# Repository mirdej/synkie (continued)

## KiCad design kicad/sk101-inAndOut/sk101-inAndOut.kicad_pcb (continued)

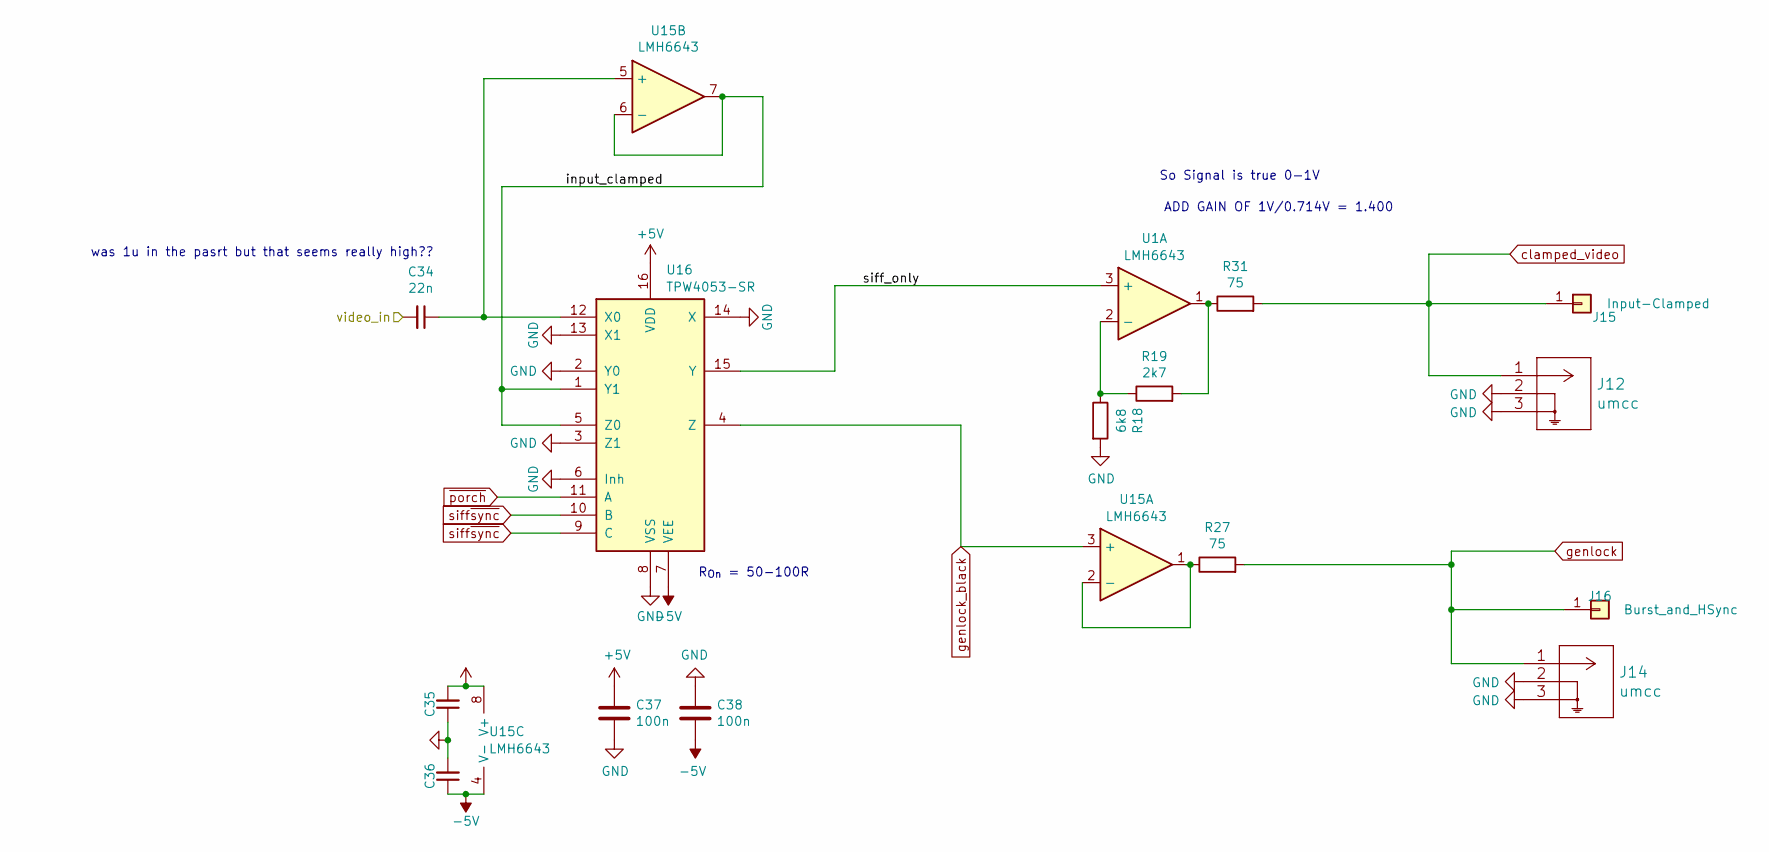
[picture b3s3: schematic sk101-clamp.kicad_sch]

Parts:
C34: 22n; C_0805_2012Metric_Pad1.15x1.40mm_HandSolder; LCSC C1729
C35, C36, C37, C38: 100n; C_0603_1608Metric; LCSC C14663
J12, J14: umcc; TE_UMCC_2337019-1; LCSC C5137195
J15: Input-Clamped; TestPoint_THTPad_D4.0mm_Drill2.0mm
J16: Burst_and_HSync; TestPoint_THTPad_D4.0mm_Drill2.0mm
R18: 6k8; R_0603_1608Metric; LCSC C23212
R19: 2k7; R_0603_1608Metric; LCSC C13167
R27, R31: 75; R_0603_1608Metric; LCSC C4275
U1, U15: LMH6643; VSSOP-8_3x3mm_P0.65mm; LCSC C478382
U16: TPW4053-SR; SOIC-16_3.9x9.9mm_P1.27mm; LCSC C7500846

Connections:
+5V: C35.2, C37.1, U15.8 (V+), U16.16 (VDD); also elsewhere on the board
-5V: C36.1, C38.2, U15.4 (V-), U16.7 (VEE); also elsewhere on the board
/Backporch-Clamp/input_clamped: U15.6 (-), U15.7, U16.1 (Y1), U16.5 (Z0)
/Backporch-Clamp/siff_only: U1.3 (+), U16.15 (Y)
/video_input_bufferd: C34.2; also elsewhere on the board
GND: C35.1, C36.2, C37.2, C38.1, J12.2, J12.3, J14.2, J14.3, R18.2, U16.2 (Y0), U16.3 (Z1), U16.6 (Inh), U16.8 (VSS), U16.13 (X1), U16.14 (X); also elsewhere on the board
unnamed: R19.2, R31.1, U1.1
unnamed: R18.1, R19.1, U1.2 (-)
unnamed: R27.1, U15.1, U15.2 (-)
unnamed: C34.1, U15.5 (+), U16.12 (X0)
clamped_video: J12.1, J15.1 (Pin_1_1), R31.2; also elsewhere on the board
genlock: J14.1, J16.1 (Pin_1_1), R27.2; also elsewhere on the board
genlock_black: U15.3 (+), U16.4 (Z); also elsewhere on the board
siff~sync: U16.9 (C), U16.10 (B); also elsewhere on the board
~porch: U16.11 (A); also elsewhere on the board

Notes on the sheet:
ADD GAIN OF 1V/0.714V = 1.400
So Signal is true 0-1V
R_{On} = 50-100R
was 1u in the pasrt but that seems really high??

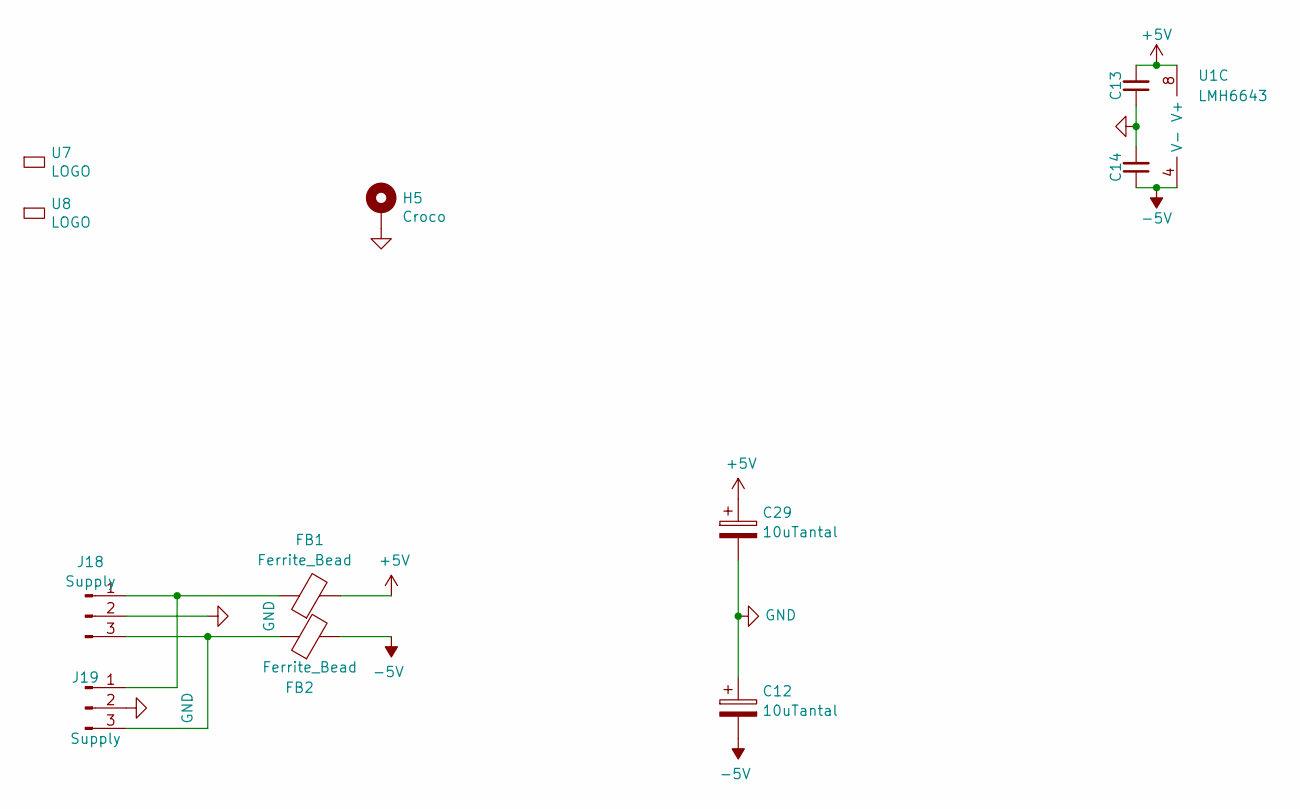
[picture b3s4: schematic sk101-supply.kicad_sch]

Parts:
C12, C29: 10uTantal; CP_EIA-3216-18_Kemet-A; LCSC C7171
C13, C14: 100n; C_0603_1608Metric; LCSC C14663
FB1, FB2: Ferrite_Bead; L_0805_2012Metric_Pad1.15x1.40mm_HandSolder; LCSC C1017
H5: Croco; CrocodileGroundPad
J18: Supply; Hirose_DF13-03P-1.25DSA_1x03_P1.25mm_Vertical
J19: Supply; Molex_KK-254_AE-6410-03A_1x03_P2.54mm_Vertical
U1: LMH6643; VSSOP-8_3x3mm_P0.65mm; LCSC C478382
U7: LOGO; logo_anyma
U8: LOGO; OSHW-Logo2_7.3x6mm_SilkScreen

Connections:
+5V: C13.2, C29.1, FB1.2, U1.8 (V+); also elsewhere on the board
-5V: C12.2, C14.1, FB2.2, U1.4 (V-); also elsewhere on the board
GND: C12.1, C13.1, C14.2, C29.2, H5.1 (1_1), J18.2, J19.2; also elsewhere on the board
unnamed: FB1.1, J18.1, J19.1
unnamed: FB2.1, J18.3, J19.3

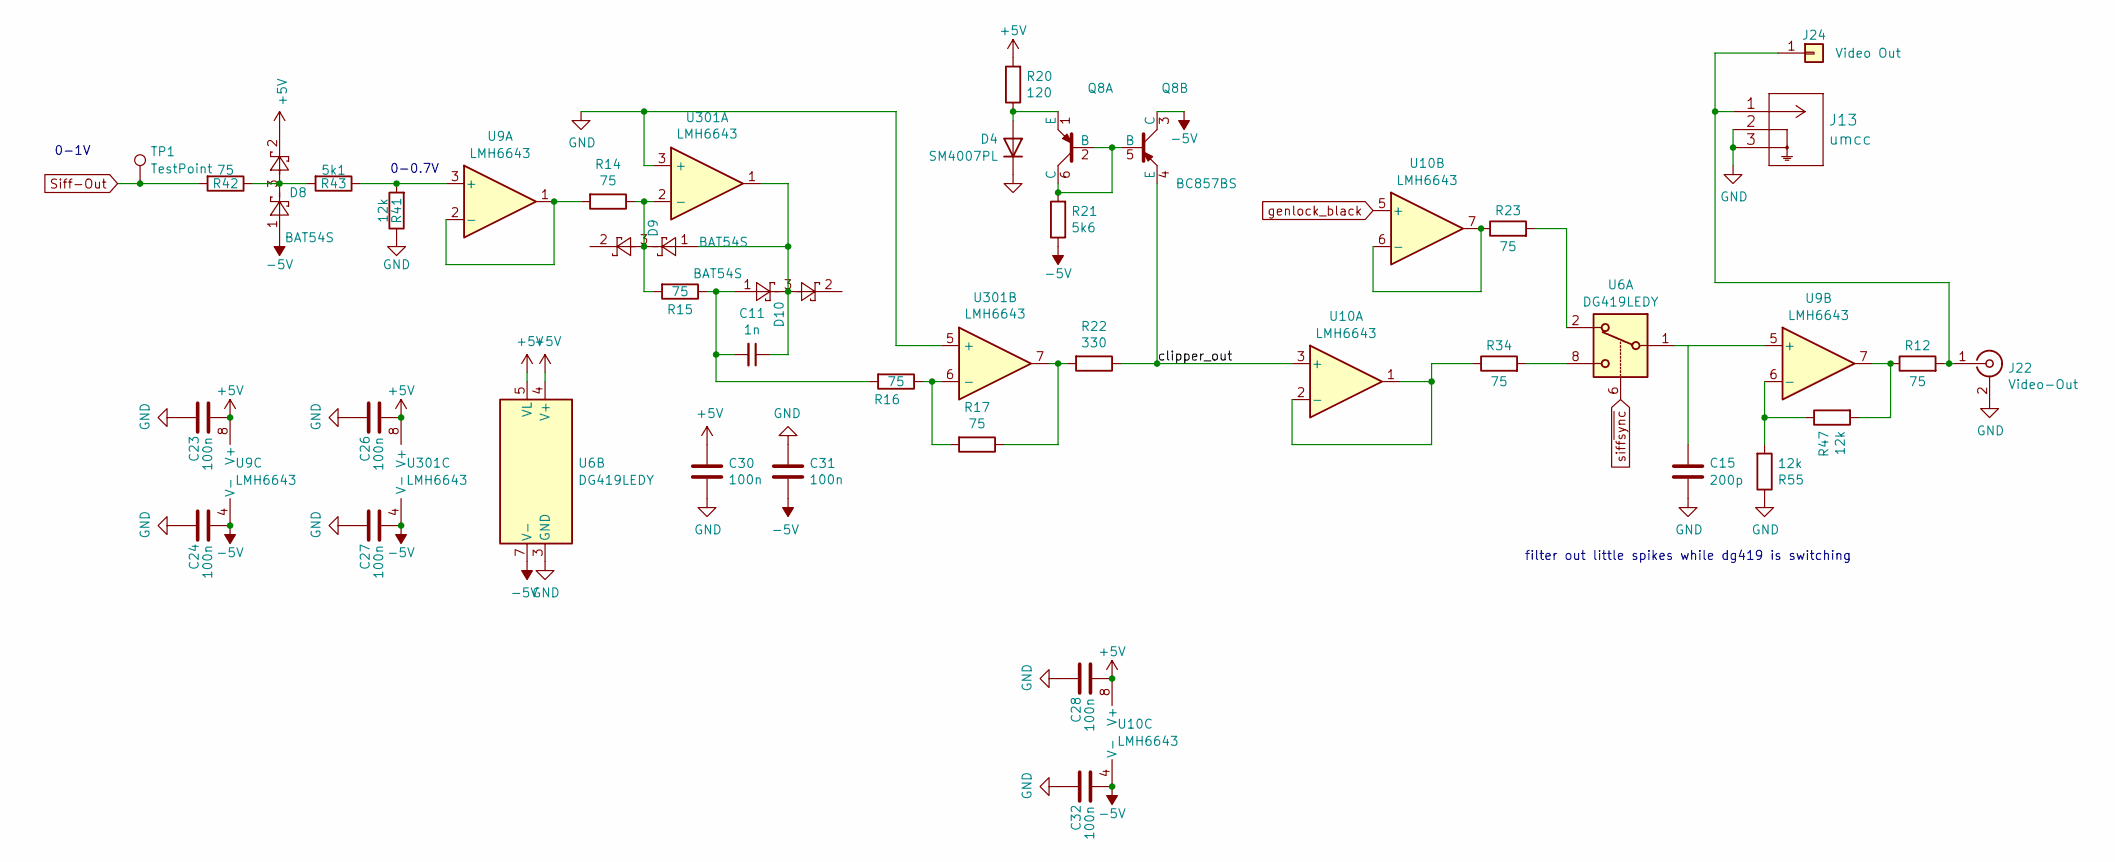
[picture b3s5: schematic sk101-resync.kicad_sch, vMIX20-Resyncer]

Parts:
C11: 1n; C_0603_1608Metric; LCSC C1588
C15: 200p; C_0603_1608Metric_Pad1.05x0.95mm_HandSolder; LCSC C1603
C23, C24, C26, C27, C28, C30, C31, C32: 100n; C_0603_1608Metric; LCSC C14663
D4: SM4007PL; D_SOD-123F; LCSC C64898
D8, D9, D10: BAT54S; SOT-23; LCSC C7420333
J13: umcc; TE_UMCC_2337019-1; LCSC C5137195
J22: Video-Out; BNC_Aliexpress
J24: Video Out; TestPoint_THTPad_D4.0mm_Drill2.0mm
Q8: BC857BS; SOT-363_SC-70-6_Handsoldering; LCSC C22381405
R12, R14, R15, R16, R17, R23, R34, R42: 75; R_0603_1608Metric; LCSC C4275
R20: 120; R_0603_1608Metric; LCSC C22787
R21: 5k6; R_0603_1608Metric; LCSC C23189
R22: 330; R_0603_1608Metric; LCSC C23138
R41, R47, R55: 12k; R_0603_1608Metric; LCSC C22790
R43: 5k1; R_0603_1608Metric; LCSC C23186
TP1: TestPoint; TestPoint_THTPad_D4.0mm_Drill2.0mm
U6: DG419LEDY; SOIC-8_3.9x4.9mm_P1.27mm; LCSC C2673265
U9, U10, U301: LMH6643; VSSOP-8_3x3mm_P0.65mm; LCSC C478382

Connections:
+5V: C23.2, C26.2, C28.2, C30.1, D8.2, R20.2, U6.4 (V+), U6.5 (VL), U9.8 (V+), U10.8 (V+), U301.8 (V+); also elsewhere on the board
-5V: C24.2, C27.2, C31.2, C32.2, D8.1, Q8.3 (C), R21.1, U6.7 (V-), U9.4 (V-), U10.4 (V-), U301.4 (V-); also elsewhere on the board
/Resyncer/clipper_out: Q8.4 (E), R22.1, U10.3 (+)
GND: C15.2, C23.1, C24.1, C26.1, C27.1, C28.1, C30.2, C31.1, C32.1, D4.1 (K), J13.2, J13.3, J22.2 (Ext), R41.1, R55.1, U6.3 (GND), U301.3 (+), U301.5 (+); also elsewhere on the board
unnamed: C11.1, D9.1, D10.3, U301.1
unnamed: C11.2, D10.1, R15.1, R16.2
unnamed: D4.2 (A), Q8.1 (E), R20.1
unnamed: D8.3, R42.1, R43.2
unnamed: J13.1, J22.1 (In), J24.1 (Pin_1_1), R12.2
unnamed: Q8.2 (B), Q8.5 (B), Q8.6 (C), R21.2
unnamed: R12.1, R47.2, U9.7
unnamed: R17.1, R22.2, U301.7
unnamed: R23.2, U6.2
unnamed: R34.2, U6.8
unnamed: R41.2, R43.1, U9.3 (+)
unnamed: R14.2, U9.1, U9.2 (-)
unnamed: C15.1, U6.1, U9.5 (+)
unnamed: R47.1, R55.2, U9.6 (-)
unnamed: R34.1, U10.1, U10.2 (-)
unnamed: R23.1, U10.6 (-), U10.7
unnamed: D9.3, R14.1, R15.2, U301.2 (-)
unnamed: R16.1, R17.2, U301.6 (-)
Siff-Out: R42.2, TP1.1 (1_1); also elsewhere on the board
genlock_black: U10.5 (+); also elsewhere on the board
siff~sync: U6.6; also elsewhere on the board

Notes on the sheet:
0-1V
filter out little spikes while dg419 is switching
0-0.7V

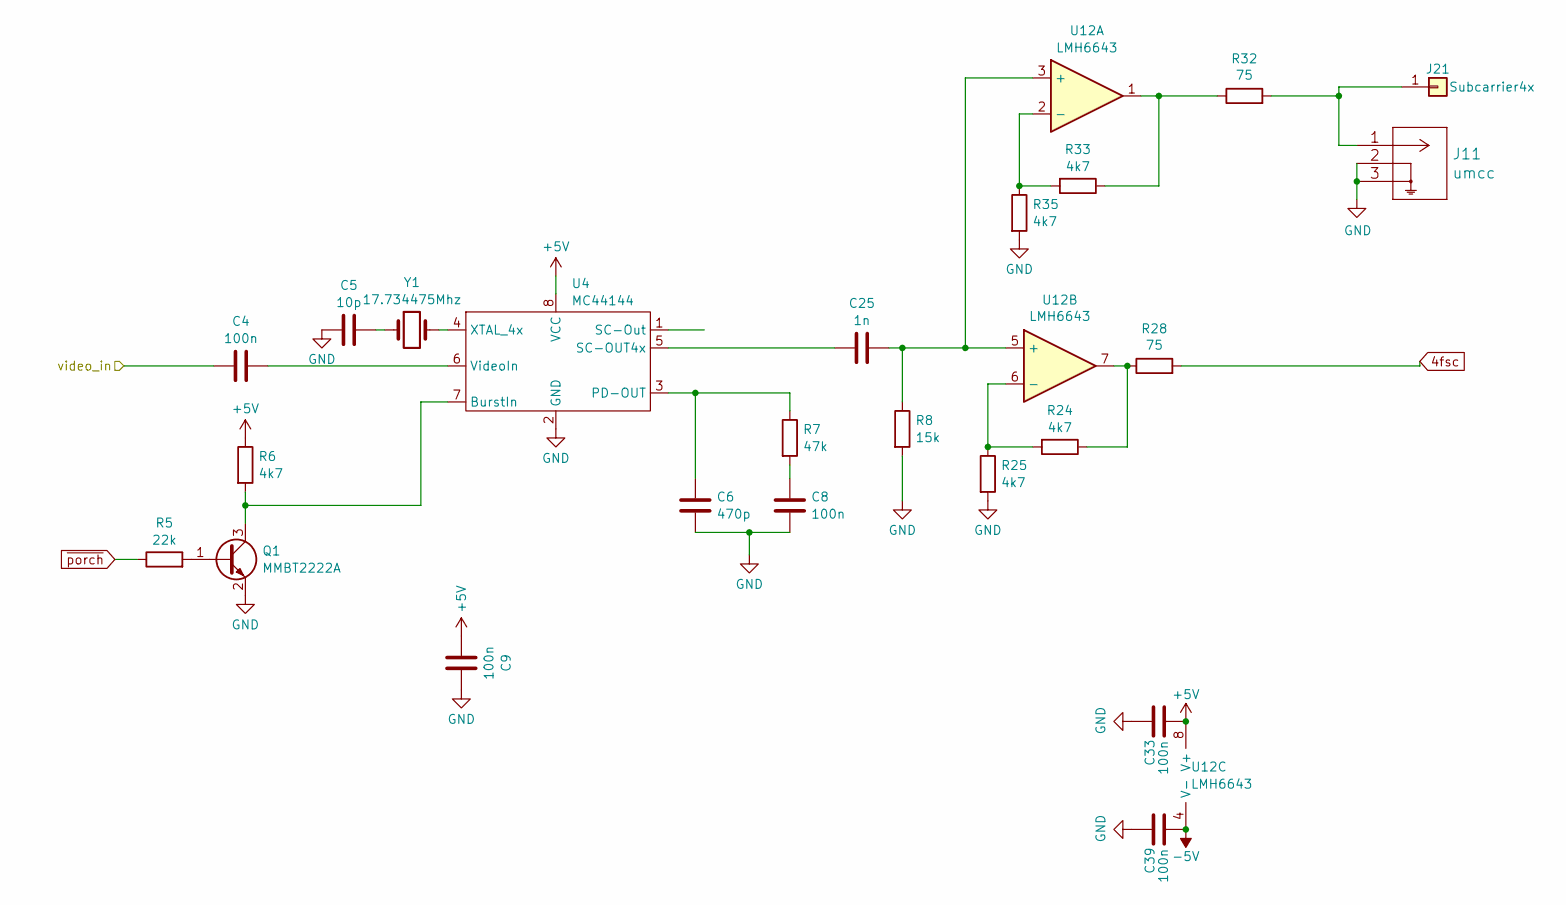
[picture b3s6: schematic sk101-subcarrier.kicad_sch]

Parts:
C4, C8, C9, C33, C39: 100n; C_0603_1608Metric; LCSC C14663
C5: 10p; C_0603_1608Metric; LCSC C1634
C6: 470p; C_0603_1608Metric; LCSC C1620
C25: 1n; C_0603_1608Metric; LCSC C1588
J11: umcc; TE_UMCC_2337019-1; LCSC C5137195
J21: Subcarrier4x; TestPoint_THTPad_D4.0mm_Drill2.0mm
Q1: MMBT2222A; SOT-23; LCSC C8512
R5: 22k; R_0603_1608Metric; LCSC C31850
R6, R24, R25, R33, R35: 4k7; R_0603_1608Metric; LCSC C23162
R7: 47k; R_0603_1608Metric; LCSC C25819
R8: 15k; R_0603_1608Metric; LCSC C22809
R28, R32: 75; R_0603_1608Metric; LCSC C4275
U4: MC44144; SOIC-8_3.9x4.9mm_P1.27mm
U12: LMH6643; VSSOP-8_3x3mm_P0.65mm; LCSC C478382
Y1: 17.734475Mhz; Crystal_SMD_HC49-SD; LCSC C22464815

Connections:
4fsc: R28.2; also elsewhere on the board
+5V: C9.1, C33.2, R6.1, U4.8 (VCC), U12.8 (V+); also elsewhere on the board
-5V: C39.2, U12.4 (V-); also elsewhere on the board
/video_input_bufferd: C4.1; also elsewhere on the board
GND: C5.1, C6.2, C8.2, C9.2, C33.1, C39.1, J11.2, J11.3, Q1.2 (E), R8.2, R25.2, R35.2, U4.2 (GND); also elsewhere on the board
unnamed: C5.2, Y1.1
unnamed: C8.1, R7.2
unnamed: J11.1, J21.1 (Pin_1_1), R32.2
unnamed: Q1.1 (B), R5.2
unnamed: Q1.3 (C), R6.2, U4.7 (BurstIn)
unnamed: R24.1, R28.1, U12.7
unnamed: R32.1, R33.1, U12.1
unnamed: C6.1, R7.1, U4.3 (PD-OUT)
unnamed: C25.1, U4.5 (SC-OUT4x)
unnamed: C4.2, U4.6 (VideoIn)
unnamed: U4.4 (XTAL_4x), Y1.2
unnamed: C25.2, R8.1, U12.3 (+), U12.5 (+)
unnamed: R33.2, R35.1, U12.2 (-)
unnamed: R24.2, R25.1, U12.6 (-)
~porch: R5.1; also elsewhere on the board

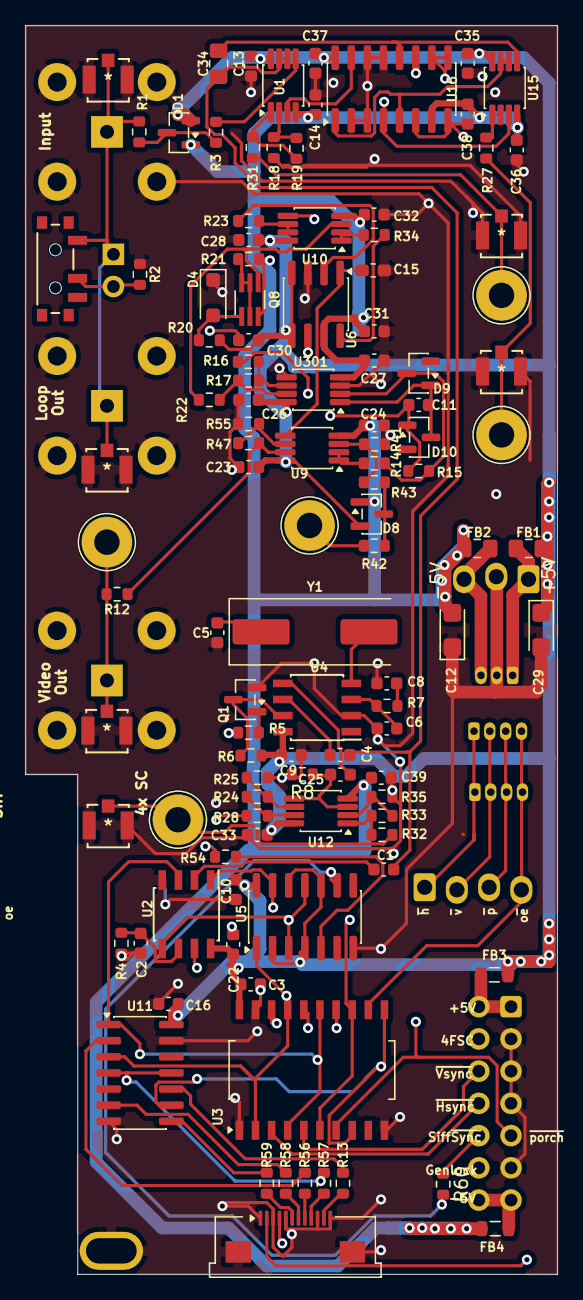
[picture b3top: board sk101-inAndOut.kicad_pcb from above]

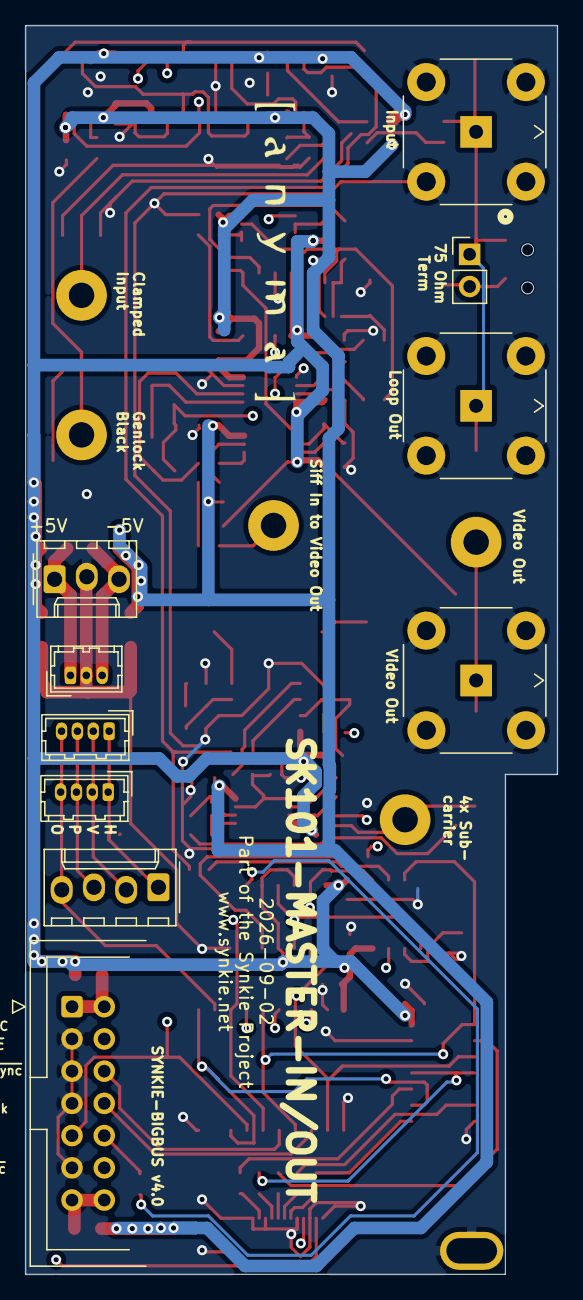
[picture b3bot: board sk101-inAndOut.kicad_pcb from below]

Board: 4 copper layers, 41.9 x 98.4 mm, 124 parts (12 on the bottom side), 83 nets.

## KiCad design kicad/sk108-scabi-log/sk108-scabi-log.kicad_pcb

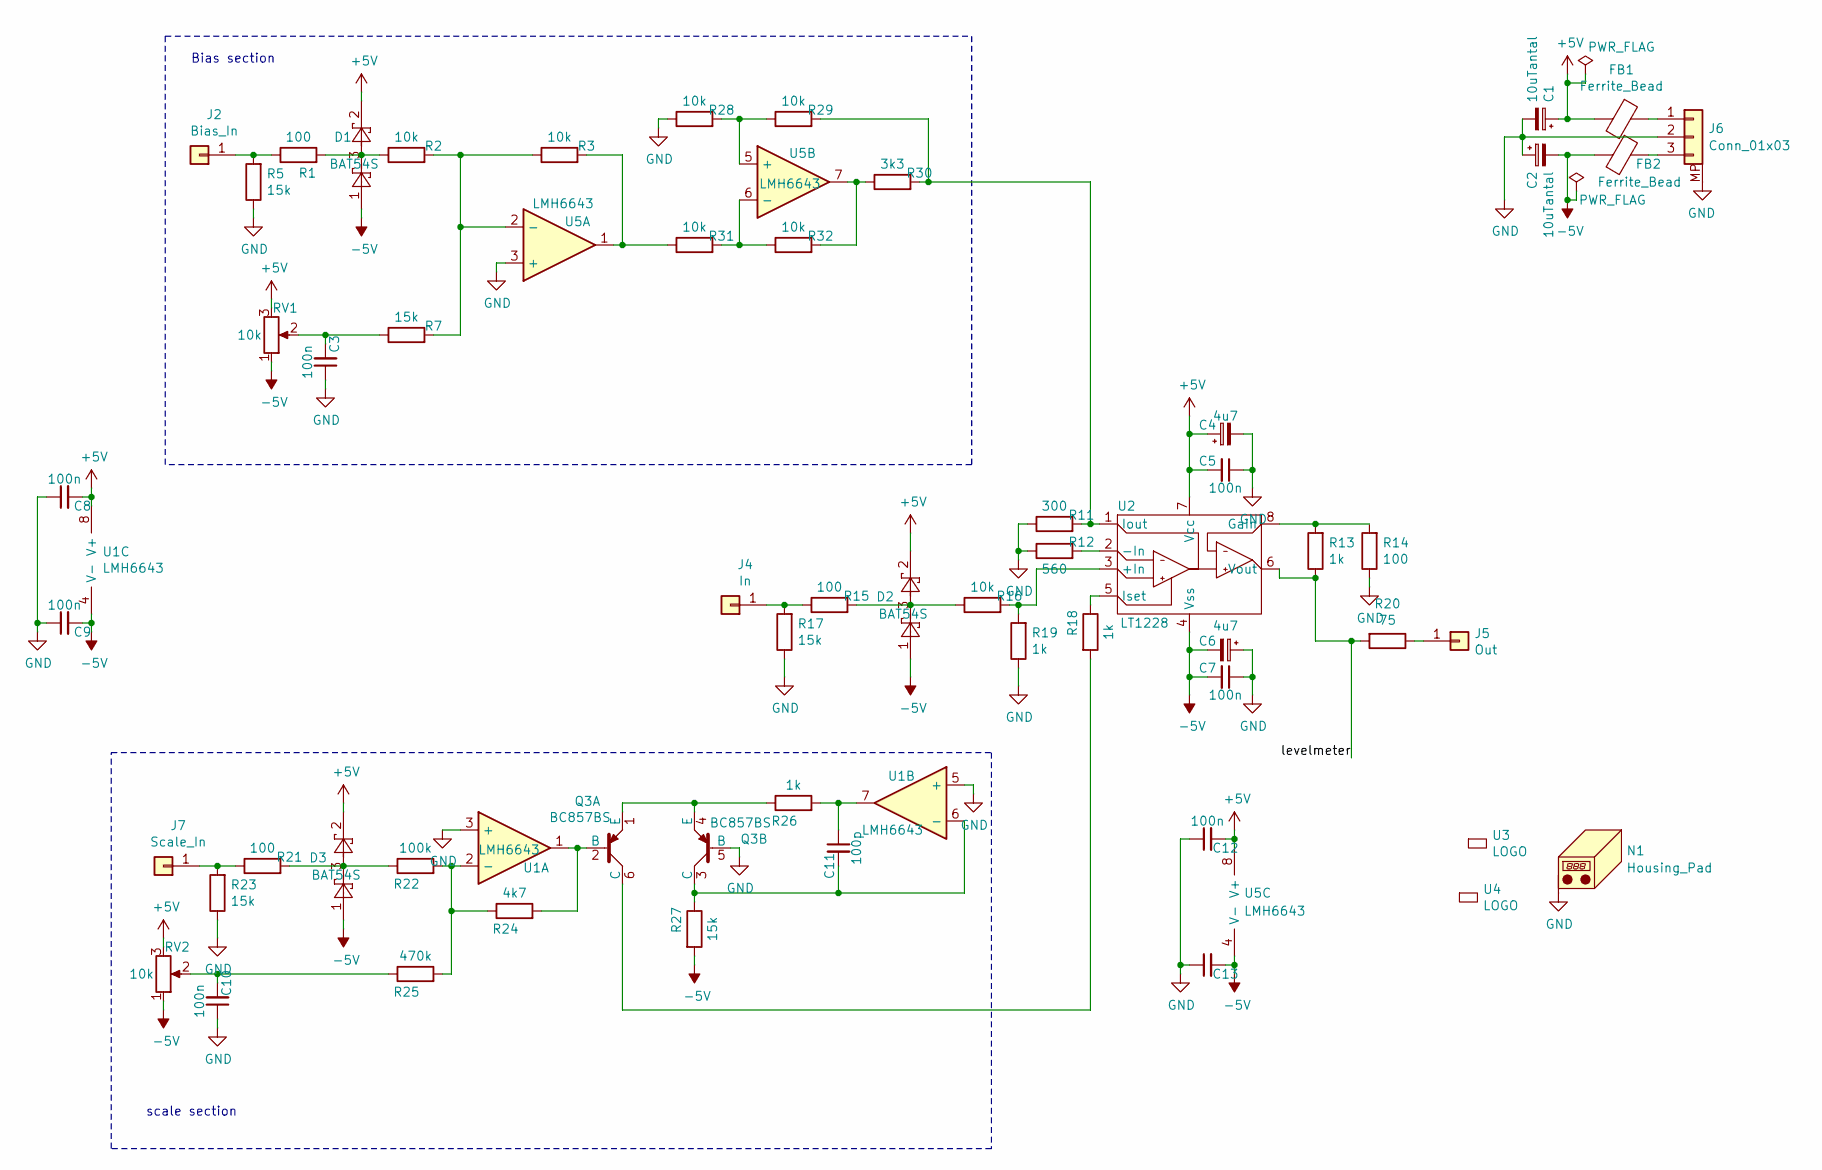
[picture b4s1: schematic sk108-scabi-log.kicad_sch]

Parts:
C1, C2: 10uTantal; CP_EIA-3216-18_Kemet-A; LCSC C7171
C3, C5, C7, C8, C9, C10, C12, C13: 100n; C_0603_1608Metric; LCSC C14663
C4, C6: 4u7; C_0805_2012Metric; LCSC C1779
C11: 100p; C_0603_1608Metric; LCSC C14858
D1, D2, D3: BAT54S; SOT-23; LCSC C8592
FB1, FB2: Ferrite_Bead; L_0805_2012Metric; LCSC C1017
J2: Bias_In; Banana2mm-Löthülse
J4: In; Banana2mm-Löthülse
J5: Out; Banana2mm-Löthülse
J6: Conn_01x03; JST_PH_B3B-PH-SM4-TB_1x03-1MP_P2.00mm_Vertical; LCSC C18077900
J7: Scale_In; Banana2mm-Löthülse
N1: Housing_Pad; Frontplate_20mm
Q3: BC857BS; SOT-363_SC-70-6_Handsoldering; LCSC C22381405
R1, R14, R15, R21: 100; R_0603_1608Metric; LCSC C22775
R2, R3, R16, R28, R29, R31, R32: 10k; R_0603_1608Metric; LCSC C25804
R5, R7, R17, R23, R27: 15k; R_0603_1608Metric; LCSC C22809
R11: 300; R_0603_1608Metric; LCSC C23025
R12: 560; R_0603_1608Metric; LCSC C23204
R13, R18, R19, R26: 1k; R_0603_1608Metric; LCSC C21190
R20: 75; R_0603_1608Metric; LCSC C4275
R22: 100k; R_0603_1608Metric; LCSC C25803
R24: 4k7; R_0603_1608Metric; LCSC C23162
R25: 470k; R_0603_1608Metric; LCSC C23178
R30: 3k3; R_0603_1608Metric; LCSC C22978
RV1, RV2: 10k; Alps_RK097_Frontplate; LCSC C25804
U1, U5: LMH6643; VSSOP-8_3x3mm_P0.65mm; LCSC C478382
U2: LT1228; SOIC-8_3.9x4.9mm_P1.27mm
U3: LOGO; logo_anyma
U4: LOGO; OSHW-Logo2_7.3x6mm_SilkScreen

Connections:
+5V: C1.1, C4.1, C5.2, C8.2, C12.2, D1.2, D2.2, D3.2, FB1.2, RV1.3, RV2.3, U1.8 (V+), U2.7 (Vcc), U5.8 (V+)
-5V: C2.2, C6.2, C7.2, C9.2, C13.2, D1.1, D2.1, D3.1, FB2.2, R27.2, RV1.1, RV2.1, U1.4 (V-), U2.4 (Vss), U5.4 (V-)
/levelmeter: R13.1, R20.2, U2.6 (Vout)
GND: C1.2, C2.1, C3.1, C4.2, C5.1, C6.1, C7.1, C8.1, C9.1, C10.1, C12.1, C13.1, J6.2, J6.MP, N1.1 (PAD_1), Q3.5 (B), R5.1, R11.1, R12.1, R14.1, R17.1, R19.1, R23.1, R28.1, U1.3 (+), U1.5 (+), U5.3 (+)
unnamed: C3.2, R7.1, RV1.2
unnamed: C10.2, R25.1, RV2.2
unnamed: D1.3, R1.2, R2.1
unnamed: D2.3, R15.2, R16.1
unnamed: D3.3, R21.2, R22.1
unnamed: J2.1 (Pin_1_1), R1.1, R5.2
unnamed: J4.1 (Pin_1_1), R15.1, R17.2
unnamed: J5.1 (Pin_1_1), R20.1
unnamed: FB1.1, J6.1
unnamed: FB2.1, J6.3
unnamed: J7.1 (Pin_1_1), R21.1, R23.2
unnamed: Q3.2 (B), R24.2, U1.1
unnamed: Q3.6 (C), R18.2
unnamed: Q3.1 (E), Q3.4 (E), R26.1
unnamed: C11.2, Q3.3 (C), R27.1, U1.6 (-)
unnamed: R22.2, R24.1, R25.2, U1.2 (-)
unnamed: C11.1, R26.2, U1.7
unnamed: R16.2, R19.2, U2.3 (+In)
unnamed: R12.2, U2.2 (-In)
unnamed: R13.2, R14.2, U2.8 (Gain)
unnamed: R11.2, R29.2, R30.2, U2.1 (Iout)
unnamed: R18.1, U2.5 (Iset)
unnamed: R2.2, R3.1, R7.2, U5.2 (-)
unnamed: R3.2, R31.1, U5.1
unnamed: R28.2, R29.1, U5.5 (+)
unnamed: R31.2, R32.1, U5.6 (-)
unnamed: R30.1, R32.2, U5.7

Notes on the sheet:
scale section
Bias section

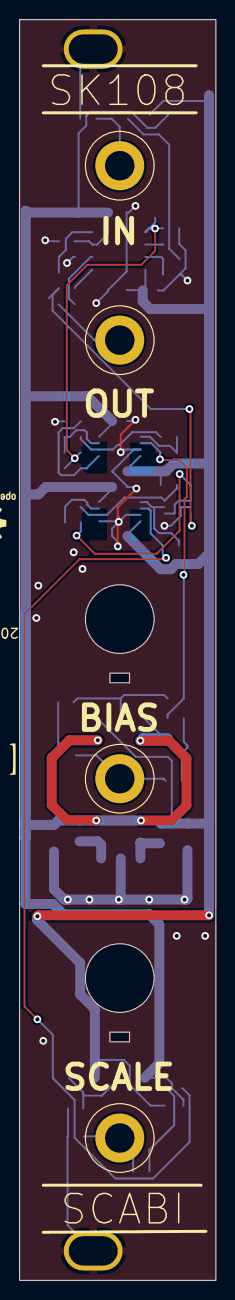
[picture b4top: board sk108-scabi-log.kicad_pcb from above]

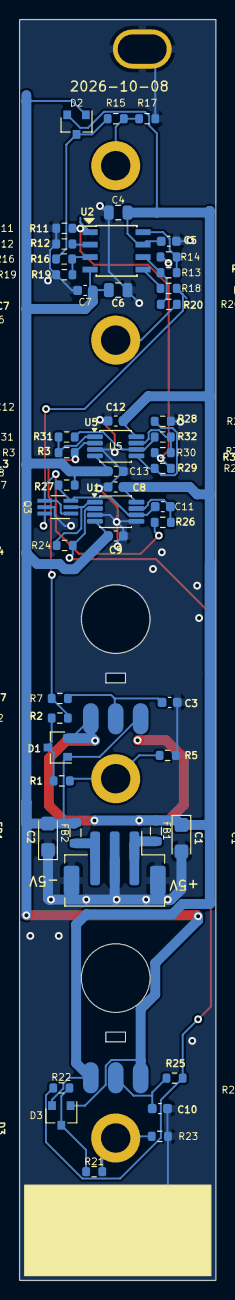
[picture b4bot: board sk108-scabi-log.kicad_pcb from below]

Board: 2 copper layers, 20.0 x 128.5 mm, 59 parts (50 on the bottom side), 31 nets.

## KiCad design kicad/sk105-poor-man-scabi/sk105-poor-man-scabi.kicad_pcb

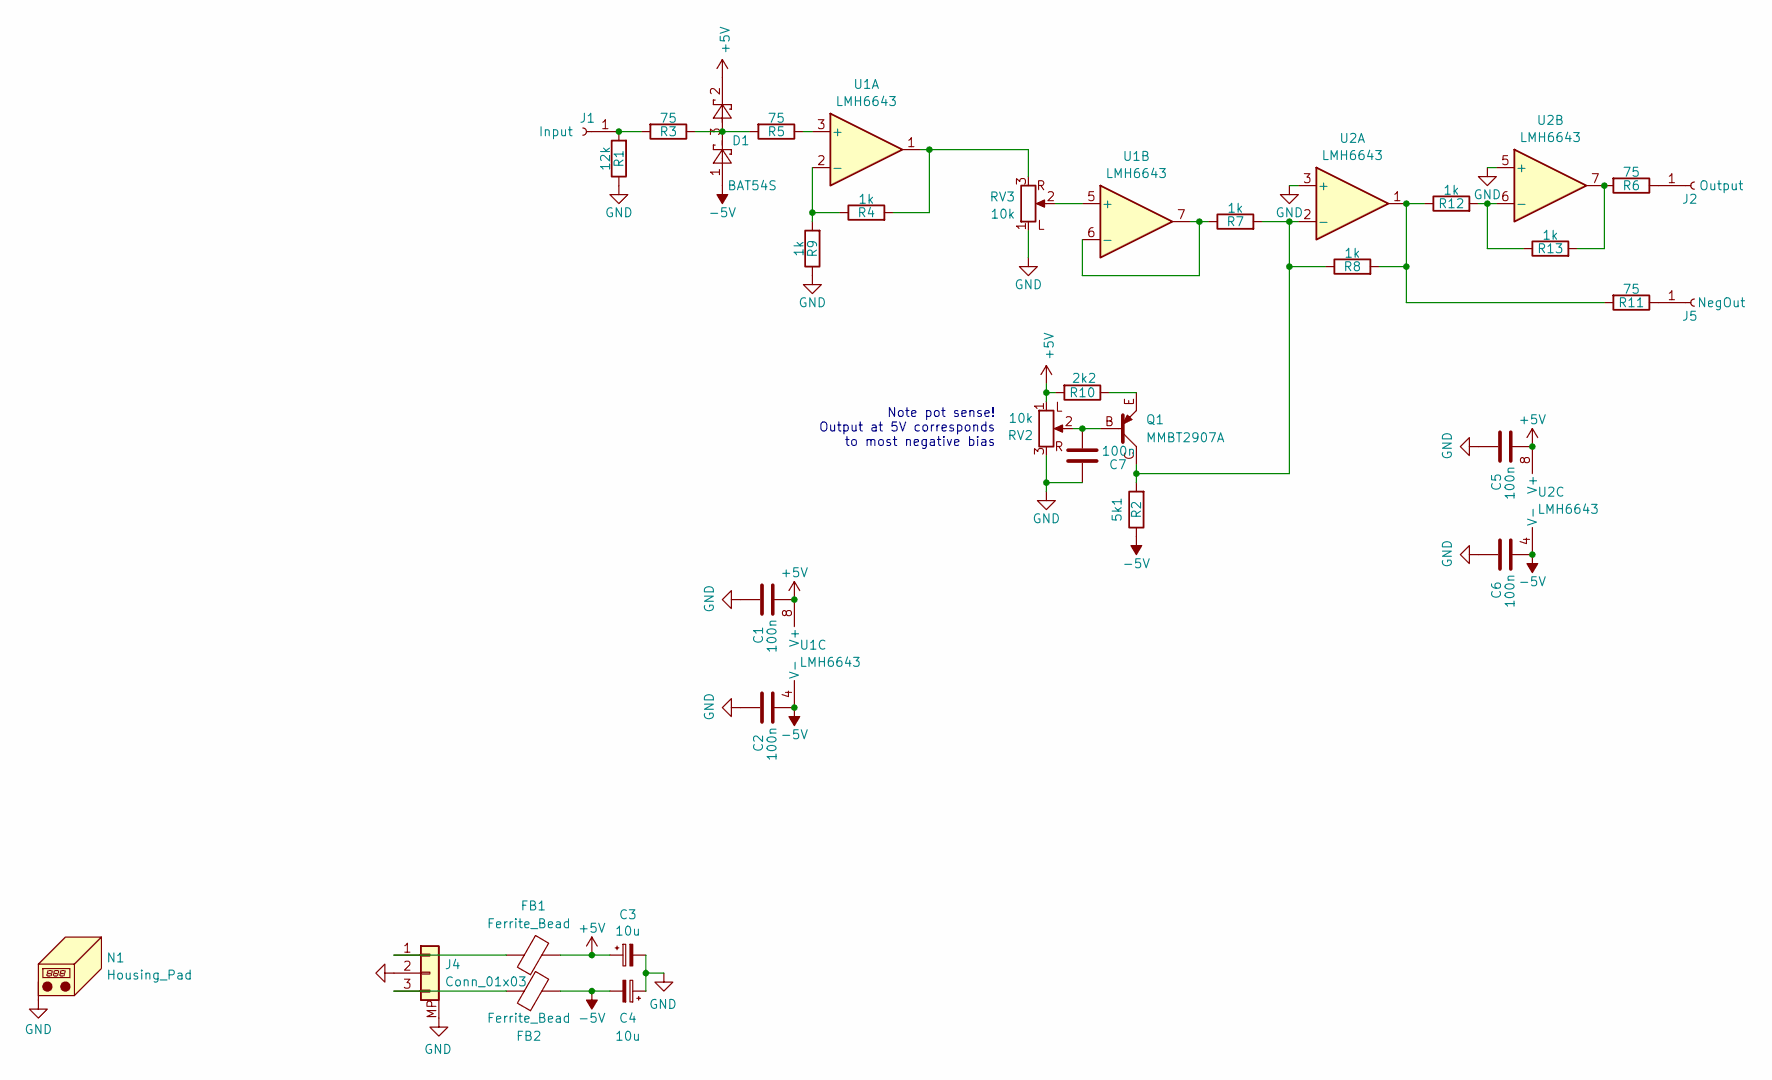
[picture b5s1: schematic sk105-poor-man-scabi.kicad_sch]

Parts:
C1, C2, C5, C6, C7: 100n; C_0402_1005Metric; LCSC C1525
C3, C4: 10u; C_0805_2012Metric; LCSC C15850
D1: BAT54S; SOT-23; LCSC C8592
FB1, FB2: Ferrite_Bead; L_0805_2012Metric; LCSC C1017
J1: Input; Banana2mm-Löthülse
J2: Output; Banana2mm-Löthülse
J4: Conn_01x03; JST_PH_B3B-PH-SM4-TB_1x03-1MP_P2.00mm_Vertical; LCSC C18077900
J5: NegOut; Banana2mm-Löthülse
N1: Housing_Pad; Frontplate_15mm
Q1: MMBT2907A; SOT-23_BEC; LCSC C40752
R1: 12k; R_0603_1608Metric; LCSC C22790
R2: 5k1; R_0603_1608Metric; LCSC C23186
R3, R5, R6, R11: 75; R_0603_1608Metric; LCSC C4275
R4, R7, R8, R9, R12, R13: 1k; R_0603_1608Metric; LCSC C21190
R10: 2k2; R_0603_1608Metric; LCSC C4190
RV2, RV3: 10k; Alps_RK097_Frontplate
U1, U2: LMH6643; SOIC-8_3.9x4.9mm_P1.27mm; LCSC C44880

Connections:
+5V: C1.2, C3.1, C5.2, D1.2, FB1.2, R10.2, RV2.1 (L), U1.8 (V+), U2.8 (V+)
-5V: C2.2, C4.2, C6.2, D1.1, FB2.2, R2.1, U1.4 (V-), U2.4 (V-)
GND: C1.1, C2.1, C3.2, C4.1, C5.1, C6.1, C7.1, J4.2, J4.MP, N1.1 (PAD_1), R1.1, R9.1, RV2.3, RV3.1 (L), U2.3 (+), U2.5 (+)
unnamed: C7.2, Q1.B, RV2.2
unnamed: D1.3, R3.1, R5.2
unnamed: J1.1 (Pin_1_1), R1.2, R3.2
unnamed: J2.1 (Pin_1_1), R6.1
unnamed: FB1.1, J4.1
unnamed: FB2.1, J4.3
unnamed: J5.1 (Pin_1_1), R11.1
unnamed: Q1.E, R10.1
unnamed: R4.2, RV3.3, U1.1
unnamed: R8.2, R11.2, R12.1, U2.1
unnamed: R6.2, R13.2, U2.7
unnamed: R5.1, U1.3 (+)
unnamed: R4.1, R9.2, U1.2 (-)
unnamed: RV3.2, U1.5 (+)
unnamed: R7.1, U1.6 (-), U1.7
unnamed: Q1.C, R2.2, R7.2, R8.1, U2.2 (-)
unnamed: R12.2, R13.1, U2.6 (-)

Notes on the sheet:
Note pot sense! Output at 5V corresponds to most negative bias

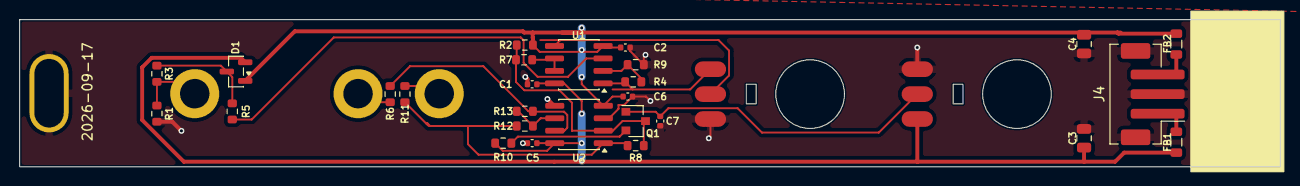
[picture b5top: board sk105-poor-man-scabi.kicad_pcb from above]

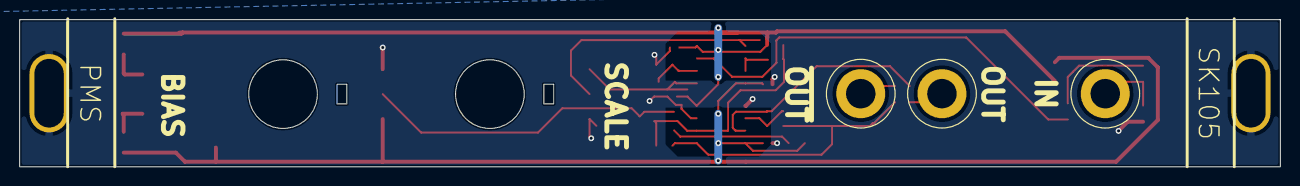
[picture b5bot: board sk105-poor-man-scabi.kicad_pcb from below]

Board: 2 copper layers, 128.5 x 15.0 mm, 33 parts (6 on the bottom side), 20 nets.
